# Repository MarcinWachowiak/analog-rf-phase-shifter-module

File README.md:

# Analog RF phase shifter module
<div align="justify">
Analog RF phase shifter modules for 2.45 GHz or 5.8 GHz. Phase shift range up to 360° for input voltage of 0 - 3.3V

**There is a discrepancy between the simulation results and testbed measurements. 
A more detailed analysis of parasitics and fine-tuning of component values is advised.**
</div>

  - **2.45 GHz distributed components version**

    **Manufactured prototypes:**

    **PCB:**

    **Simualtion results:**

    <br>

  - **2.45 GHz discrete components version**

    **Manufactured prototypes:**

    **PCB:**

    **Simualtion results:**

    <br>

  - **5.8 GHz distributed components version**

    **Manufactured prototypes:**

    **PCB:**

    **Simualtion results:**

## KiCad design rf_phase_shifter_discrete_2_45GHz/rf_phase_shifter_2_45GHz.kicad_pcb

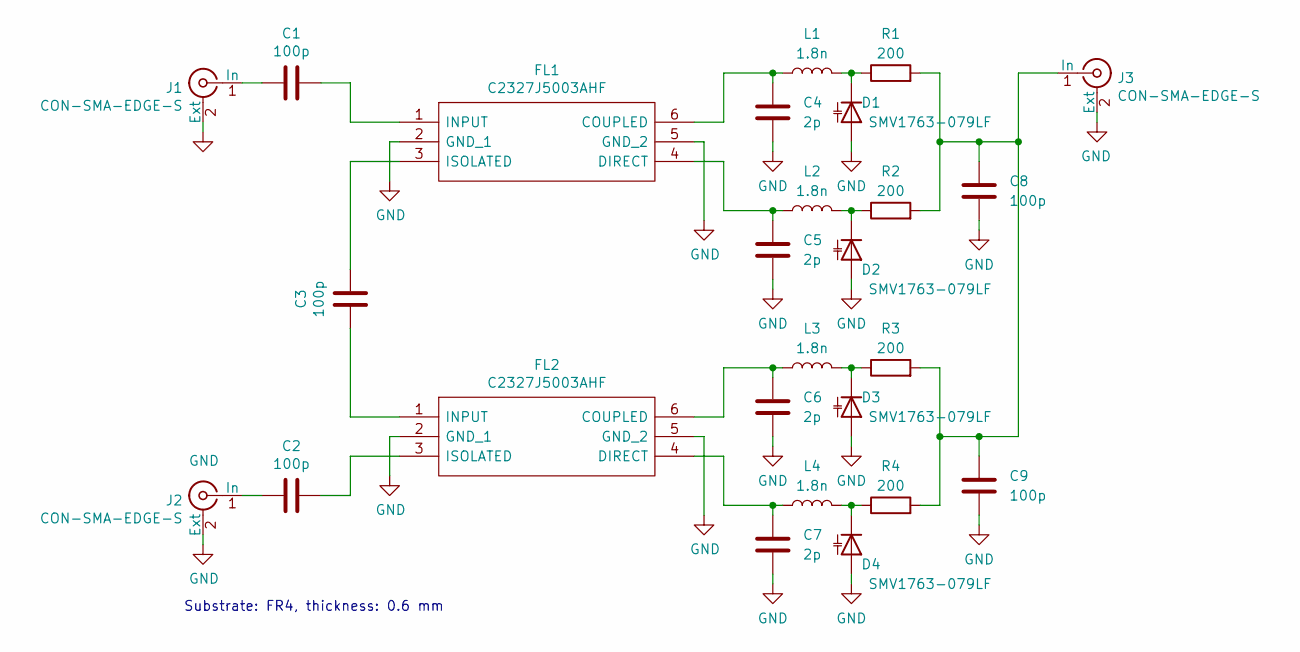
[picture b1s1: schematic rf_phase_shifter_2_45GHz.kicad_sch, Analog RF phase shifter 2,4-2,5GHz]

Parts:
C1, C2, C3, C8, C9: 100p; C_0603_1608Metric
C4, C5, C6, C7: 2p; C_0603_1608Metric
D1, D2, D3, D4: SMV1763-079LF; D_SOD-523
FL1, FL2: C2327J5003AHF; Manufacturer_Part_Number C2327J5003AHF
J1, J2, J3: CON-SMA-EDGE-S; digikey description CONN SMA JACK STR EDGE MNT
L1, L2, L3, L4: 1.8n; L_0603_1608Metric
R1, R2, R3, R4: 200; R_0603_1608Metric

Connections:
GND: C4.2, C5.2, C6.2, C7.2, C8.2, C9.2, D1.2 (A), D2.2 (A), D3.2 (A), D4.2 (A), FL1.2 (GND_1), FL1.5 (GND_2), FL2.2 (GND_1), FL2.5 (GND_2), J1.2 (Ext), J2.2 (Ext), J3.2 (Ext)
unnamed: C1.1, FL1.1 (INPUT)
unnamed: C1.2, J1.1 (In)
unnamed: C2.1, J2.1 (In)
unnamed: C2.2, FL2.3 (ISOLATED)
unnamed: C3.1, FL2.1 (INPUT)
unnamed: C3.2, FL1.3 (ISOLATED)
unnamed: C4.1, FL1.6 (COUPLED), L1.1
unnamed: C5.1, FL1.4 (DIRECT), L2.1
unnamed: C6.1, FL2.6 (COUPLED), L3.1
unnamed: C7.1, FL2.4 (DIRECT), L4.1
unnamed: C8.1, C9.1, J3.1 (In), R1.2, R2.2, R3.2, R4.2
unnamed: D1.1 (K), L1.2, R1.1
unnamed: D2.1 (K), L2.2, R2.1
unnamed: D4.1 (K), L4.2, R4.1
unnamed: D3.1 (K), L3.2, R3.1

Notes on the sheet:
Substrate: FR4, thickness: 0.6 mm

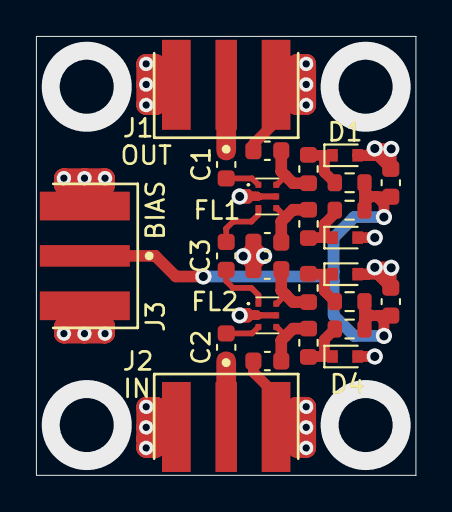
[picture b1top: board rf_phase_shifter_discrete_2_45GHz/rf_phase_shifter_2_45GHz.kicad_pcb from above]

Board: 2 copper layers, 21.1 x 24.4 mm, 26 parts (0 on the bottom side), 16 nets.

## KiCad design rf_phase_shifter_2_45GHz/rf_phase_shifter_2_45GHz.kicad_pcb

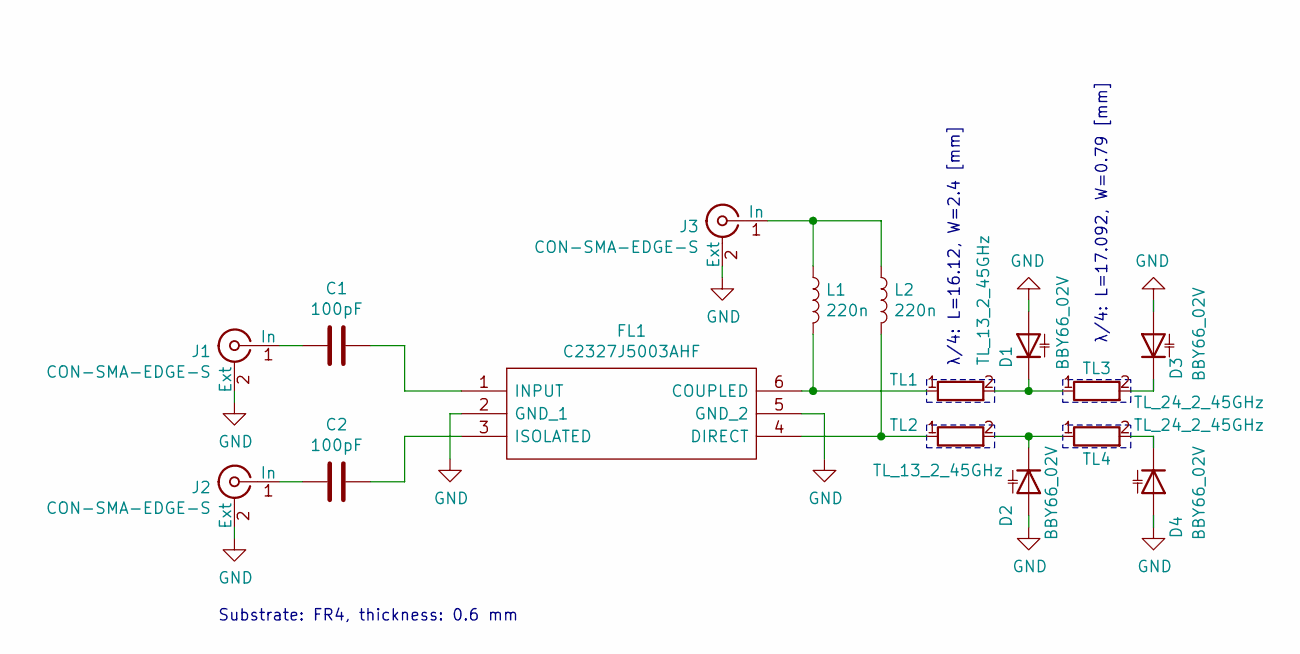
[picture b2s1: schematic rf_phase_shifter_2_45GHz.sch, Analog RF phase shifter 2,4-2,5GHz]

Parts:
C1, C2: 100pF; C_0603_1608Metric
D1, D2, D3, D4: BBY66_02V; D_SOD-523
FL1: C2327J5003AHF; Manufacturer_Part_Number C2327J5003AHF
J1, J2, J3: CON-SMA-EDGE-S; digikey description CONN SMA JACK STR EDGE MNT
L1, L2: 220n; L_0603_1608Metric
TL1, TL2: TL_13_2_45GHz
TL3, TL4: TL_24_2_45GHz

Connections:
GND: D1.2 (A), D2.2 (A), D3.2 (A), D4.2 (A), FL1.2 (GND_1), FL1.5 (GND_2), J1.2 (Ext), J2.2 (Ext), J3.2 (Ext)
unnamed: C1.1, FL1.1 (INPUT)
unnamed: C1.2, J1.1 (In)
unnamed: C2.1, J2.1 (In)
unnamed: C2.2, FL1.3 (ISOLATED)
unnamed: D1.1 (K), TL1.2, TL3.1
unnamed: D2.1 (K), TL2.2, TL4.1
unnamed: D3.1 (K), TL3.2
unnamed: D4.1 (K), TL4.2
unnamed: FL1.4 (DIRECT), L2.2, TL2.1
unnamed: FL1.6 (COUPLED), L1.2, TL1.1
unnamed: J3.1 (In), L1.1, L2.1

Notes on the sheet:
λ/4: L=16.12, W=2.4 [mm]
λ/4: L=17.092, W=0.79 [mm]
Substrate: FR4, thickness: 0.6 mm

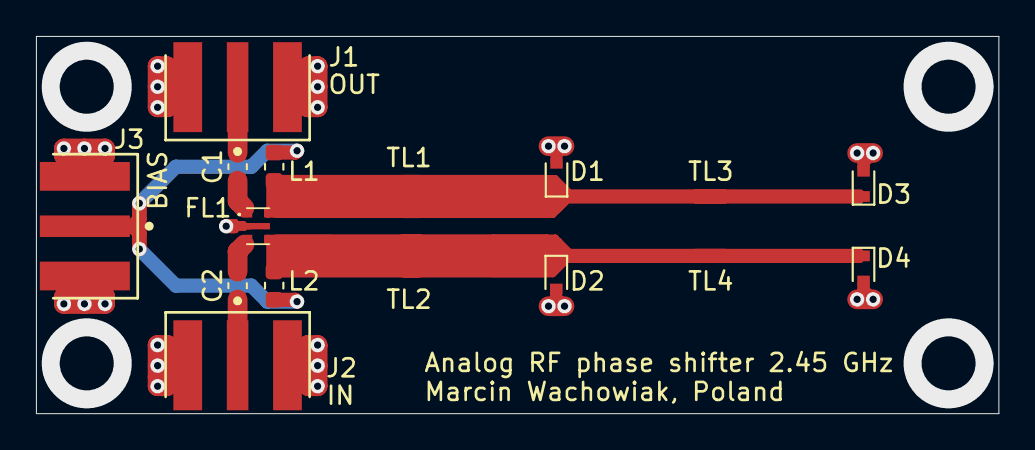
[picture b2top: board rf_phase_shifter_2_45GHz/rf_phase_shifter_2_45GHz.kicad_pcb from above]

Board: 2 copper layers, 53.5 x 21.0 mm, 16 parts (0 on the bottom side), 12 nets.

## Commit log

2021-04-01 Finished sch
2021-04-16 Update rf_phase_shifter_2_45GHz.kicad_pcb
    update
2021-05-03 updated libs
2021-09-11 qucs sim
2021-09-11 sim libs
2021-09-15 added s4p models for couplers
2021-09-19 Remove ignored files
2021-09-26 finished impedance tuning
2021-09-26 finishing touches
2021-09-26 pcb init works
2021-09-27 finished pcb layouts
2021-09-27 added pcb images
2021-09-27 fabrication fixes
2021-10-23 added info about substrate thickness
2021-11-01 Replaced unreal BBY66 model
2021-11-13 finished optimizing 2.4GHZ PH
2021-11-13 finished 5.5GHZ PH optimization
2021-11-13 Finished layout of second prototypes
2021-11-13 removed log files
2021-11-28 Added init testbench and simulation images
2022-02-19 Vin, Vout test with ADALM1000
2022-02-20 Initial testbench works
2022-02-20 Added some test plots
2022-10-29 Update license
2022-11-19 Prepare repo for discrete component version
2022-11-22 prepare qucs sim files for new schematic
2022-11-22 Initial tests after installing QUCS
2022-11-25 Fixed schematic, added parasitics and initial LC sweeps
2022-12-02 added simultaneous C and L tuning
2022-12-03 update simulations
2022-12-03 Designed pcb for discrete component version, generated gerbers and updated docs
2022-12-10 remove backup files
2022-12-10 update gitignore not to track jupyter checkpoints
2022-12-31 Added testbench results of manufactured prototypes
2022-12-31 Updated readme with new prototype
2022-12-31 rearange simulation files and add result img
2022-12-31 replace some images
